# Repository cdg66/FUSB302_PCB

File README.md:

View this project on [CADLAB.io](https://cadlab.io/project/27529). 

# FUSB302_PCB

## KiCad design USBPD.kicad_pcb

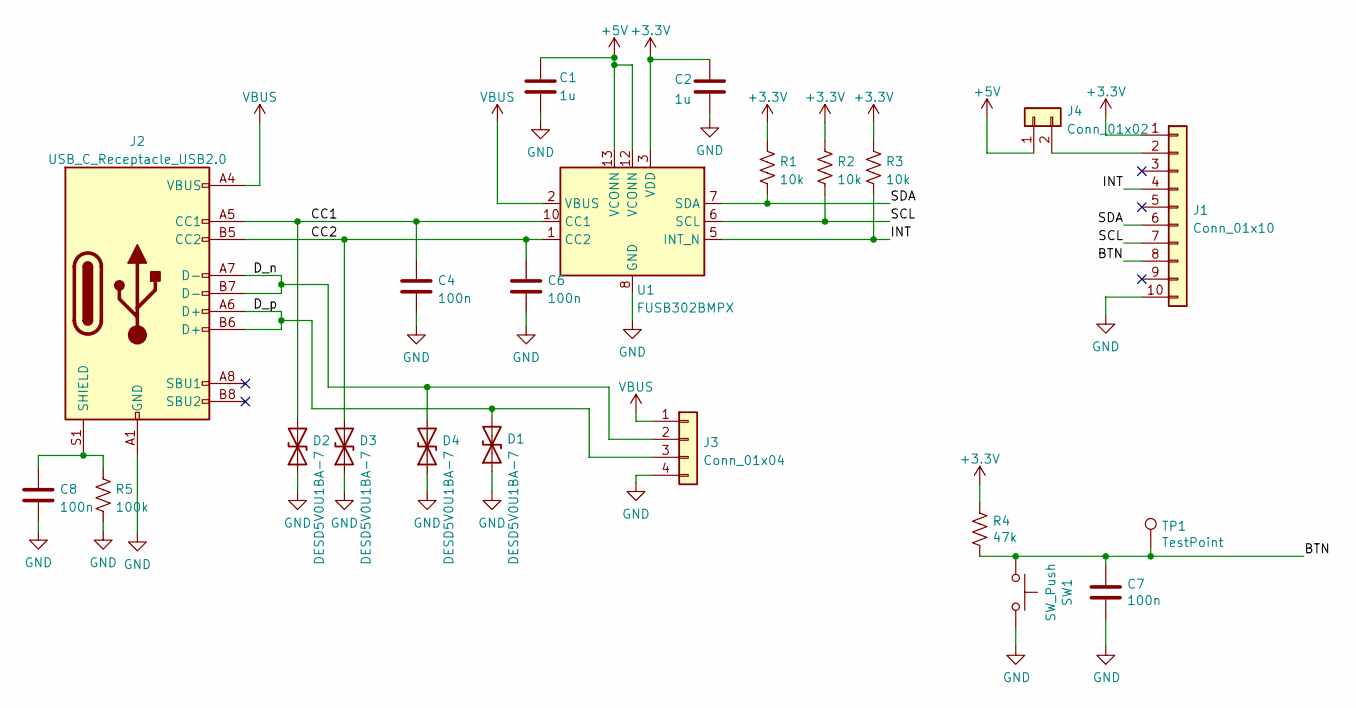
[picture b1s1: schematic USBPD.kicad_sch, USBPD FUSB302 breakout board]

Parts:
C1, C2: 1u; C_0603_1608Metric
C4, C6, C7, C8: 100n; C_0603_1608Metric
D1, D2, D3, D4: DESD5V0U1BA-7; D_SOD-323
J1: Conn_01x10; PinHeader_1x10_P2.54mm_Vertical
J2: USB_C_Receptacle_USB2.0; USB_C_Receptacle_GCT_USB4085
J3: Conn_01x04; PinHeader_1x04_P2.54mm_Vertical
J4: Conn_01x02; PinHeader_1x02_P2.54mm_Vertical
R1, R2, R3: 10k; R_0603_1608Metric
R4: 47k; R_0603_1608Metric
R5: 100k; R_0603_1608Metric
SW1: SW_Push; SW_SPST_TL3342
TP1: TestPoint; TestPoint_Pad_1.0x1.0mm
U1: FUSB302BMPX; WQFN-14-1EP_2.5x2.5mm_P0.5mm_EP1.45x1.45mm

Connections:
+3V3: C2.1, J1.1, R1.1, R2.1, R3.1, R4.1, U1.3 (VDD), U1.4 (VDD)
+5V: C1.1, J4.1, U1.12 (VCONN), U1.13 (VCONN)
/BTN: C7.1, J1.8, R4.2, SW1.1, TP1.1
/CC1: C4.1, D2.2 (A2), J2.A5 (CC1), U1.10 (CC1), U1.11 (CC1)
/CC2: C6.1, D3.2 (A2), J2.B5 (CC2), U1.1 (CC2), U1.14 (CC2)
/D_n: D4.2 (A2), J2.A7 (D-), J2.B7 (D-), J3.2
/D_p: D1.2 (A2), J2.A6 (D+), J2.B6 (D+), J3.3
/INT: J1.4, R3.2, U1.5 (INT_N)
/SCL: J1.7, R2.2, U1.6 (SCL)
/SDA: J1.6, R1.2, U1.7 (SDA)
GND: C1.2, C2.2, C4.2, C6.2, C7.2, C8.2, D1.1 (A1), D2.1 (A1), D3.1 (A1), D4.1 (A1), J1.10, J2.A1 (GND), J2.A12 (GND), J2.B1 (GND), J2.B12 (GND), J3.4, R5.2, SW1.2, U1.8 (GND), U1.9 (GND), U1.15 (GND)
unnamed: C8.1, J2.S1 (SHIELD), R5.1
unnamed: J1.2, J4.2
VBUS: J2.A4 (VBUS), J2.A9 (VBUS), J2.B4 (VBUS), J2.B9 (VBUS), J3.1, U1.2 (VBUS)

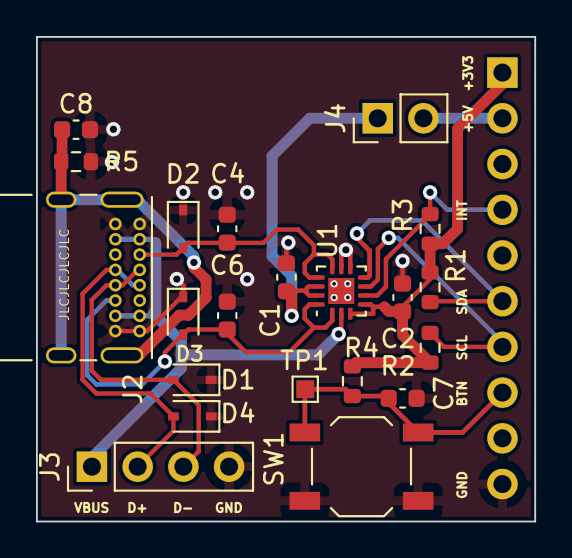
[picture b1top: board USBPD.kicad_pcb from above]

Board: 2 copper layers, 27.7 x 26.9 mm, 22 parts (1 on the bottom side), 14 nets.

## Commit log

2022-09-30 change 100nF to 470pf
2023-11-17 Backlink to CADLAB.io has been added.

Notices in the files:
USBPD.kicad_sch:
All rights reserved
